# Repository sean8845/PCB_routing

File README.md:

# **PCB\_routing**

## Basic Astar

### Execution Workflow
The routing process is divided into two main stages: clearing the board and generating new routes.

#### 1\. Clear Existing Tracks (Rip-up)

- Before running the routing algorithm, you must remove any existing tracks or vias to create a clean workspace.
- **Script**: basic\_Astar/ripup.py
- **Action**: This script reads your original .kicad\_pcb file, strips away all pre-existing routing data, and saves a clean version to be used as the input for the router.

#### 2\. Execute A\* Routing Logic

- Once the board is clear, you can run the pathfinding algorithm to connect the netlist.
- **Available Scripts**:

    -- **routing\_4direction.py**: Restricts routing to horizontal and vertical movements only. Only 2-Layers is allowed.

    -- **routing_8direction.py**: Allows diagonal movement for more efficient and flexible paths. Only 2-Layers is allowed.

    -- **routing_8direction_multi_layer.py**: Allows multi-layers.
    
- **Action**: The script calculates the shortest path between pins based on grid coordinates and writes the new track data back into a KiCad-compatible file.

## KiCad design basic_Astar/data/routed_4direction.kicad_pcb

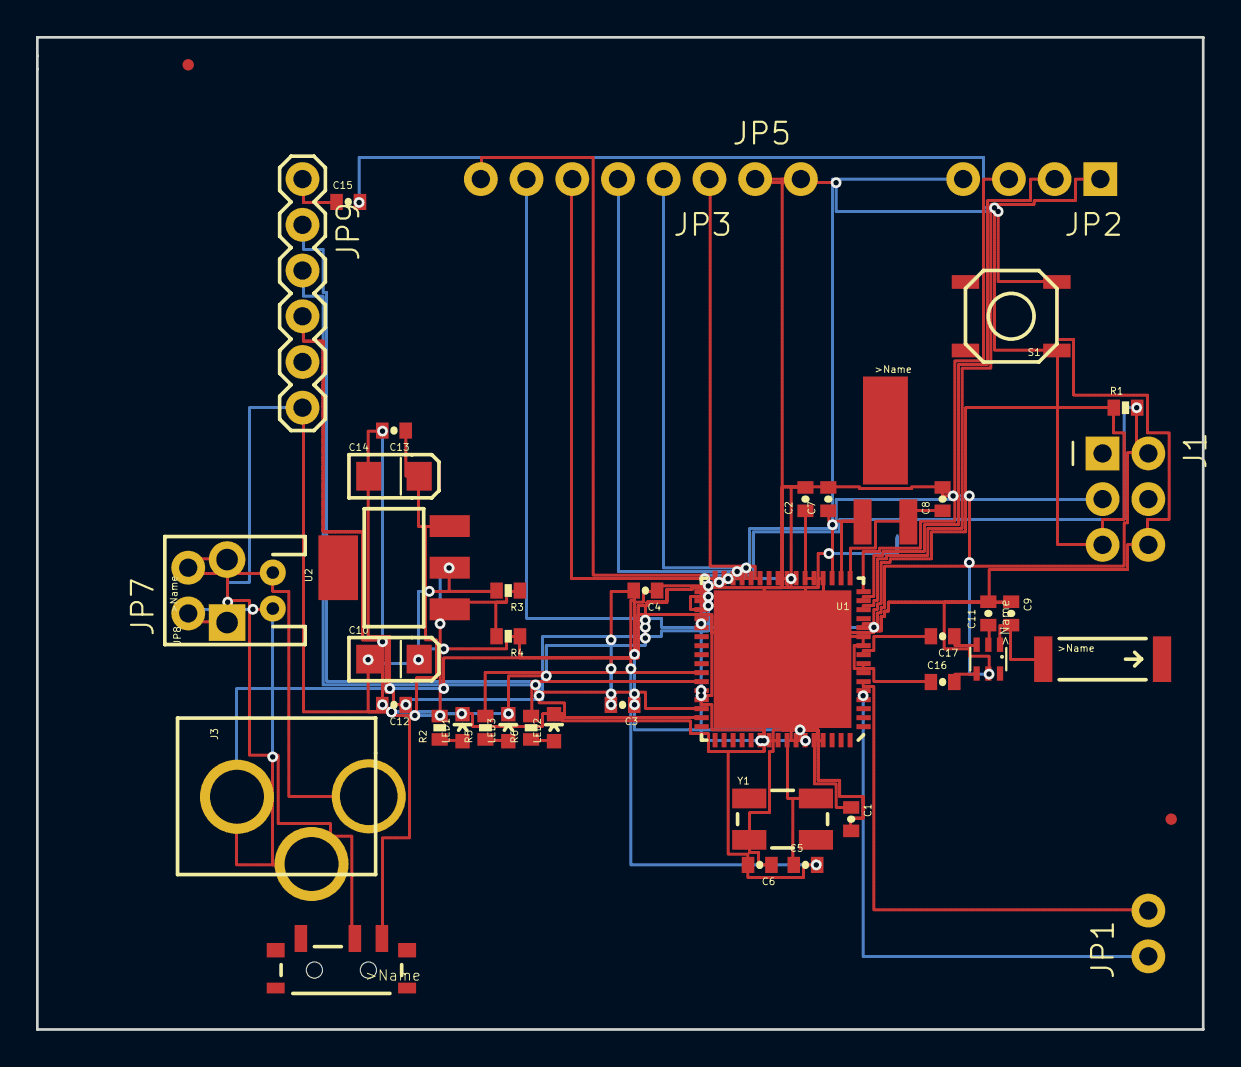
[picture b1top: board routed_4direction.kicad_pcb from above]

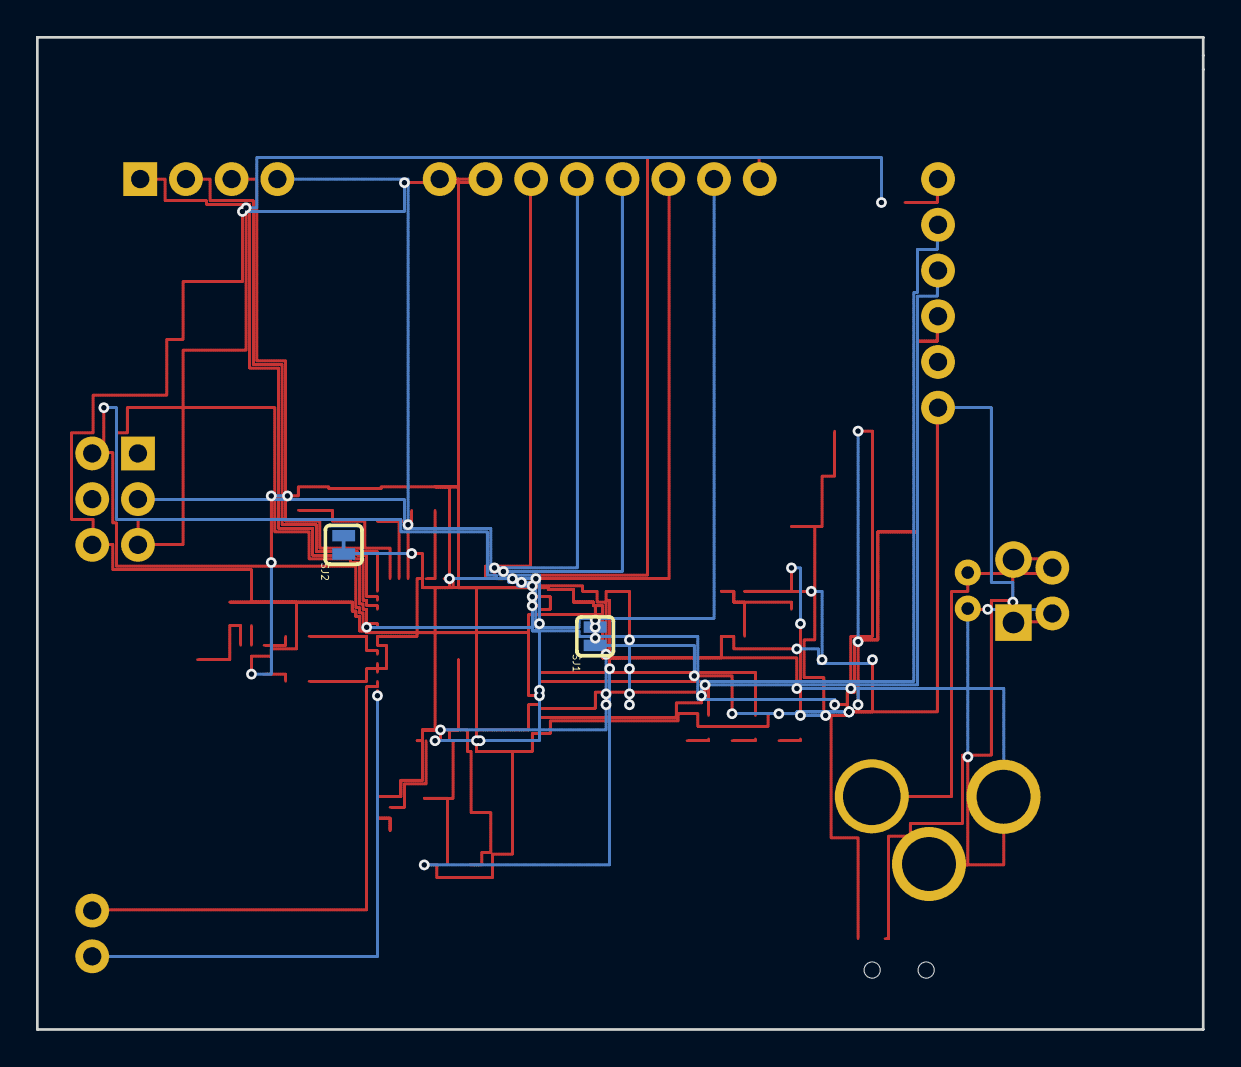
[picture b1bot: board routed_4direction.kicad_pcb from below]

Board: 2 copper layers, 64.8 x 55.1 mm, 48 parts (2 on the bottom side), 39 nets.

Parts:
A1: ANTENNA2SMD5; ANTENNA-CHIP5
B1: 748421245; BALUN
C1, C2, C3, C4, C12: 1uF; 0402-CAP
C5, C6, C7, C8: 12pF; 0402-CAP
C9: 0.75pF; 0402-CAP
C10, C14: 10uF; EIA3216
C11: 22pF; 0402-CAP
C13, C15: 0.1uF; 0402-CAP
C16, C17: JUMP; 0402-CAP
FID1, FID2: FIDUCIALUFIDUCIAL; MICRO-FIDUCIAL
J1: ISP; 2X3-NS
J3: POWER_JACKPTH_LOCK; POWER_JACK_PTH_LOCK
JP1, JP5, JP7: 1X02_NO_SILK
JP2: 1X04_NO_SILK
JP3: 1X06_NS
JP6: JST-2-PTH
JP8: SCREWTERMINAL-3.5MM-2-NS
JP9: FTDI; FTDI_BASIC
LED1: RED; LED-0603
LED2, LED3: GREEN; LED-0603
R1: 10k; 0402-RES
R2: 1k; 0402-RES
R3: 240; 0402-RES
R4: 390; 0402-RES
R5, R6: 330; 0402-RES
S1: TACTILE_SWITCH_SMD
S2: SWITCH-SPST-SMD-A
SJ1, SJ2: SJ_2S-TRACE
U1: ATMEGA128RFA1; QFN-64
U2: LM1117; SOT223
Y1: 16MHz; CRYSTAL-SMD-5X3
Y2: 32.768kHz; CRYSTAL-32KHZ-SMD

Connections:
3.3V: C3.1, C4.1, C10.A, C12.1, J1.2, JP9.VCC, R1.2, R2.2, R3.2, U1.23, U1.34, U1.44, U1.54, U1.59, U2.2
A6: JP1.1, U1.5
A7: JP1.2, U1.6
AVDD: C1.1, U1.60
DTR: C15.1, JP9.DTR
DVDD: C2.1, U1.21, U1.22
FB: R3.1, R4.2, U2.1
GND: B1.5, C1.2, C2.2, C3.2, C4.2, C5.2, C6.2, C7.2, C8.2, C9.1, C10.C, C11.2, C12.2, C13.2, C14.C, J1.6, J3.GND, J3.GNDBREAK, JP5.1, JP5.2, JP6.1, JP7.1, JP8.1, JP9.GND, LED1.C, LED2.C, LED3.C, R4.1, S1.3, SJ1.1, SJ1.2, SJ2.1, SJ2.2, U1.7, U1.10, U1.11, U1.20, U1.24, U1.33, U1.35, U1.45, U1.55, U1.58, U1.61, U1.65
unnamed: LED1.A, R2.1
unnamed: C5.1, U1.57, Y1.3
unnamed: C6.1, U1.56, Y1.1
unnamed: C7.1, U1.18, Y2.X1
unnamed: C8.1, U1.17, Y2.X2
unnamed: B1.2, C11.1
unnamed: LED3.A, R5.1
unnamed: J3.PWR, JP6.2, JP7.2, JP8.2, S2.2
unnamed: B1.4, C16.2
unnamed: B1.3, C17.1
unnamed: LED2.A, R6.1
PB6: R5.2, U1.42
PB7: R6.2, U1.43
PD4: JP3.3, U1.29
PD5: JP3.4, U1.30
PD6: JP3.5, U1.31
PD7: JP3.6, U1.32
PG0: JP2.1, U1.14
PG1: JP2.2, U1.15
PG2: JP2.3, U1.16
PG5: JP2.4, U1.19
RESET: C15.2, J1.5, R1.1, S1.1, U1.12
RFANT: A1.FEED, B1.1, C9.2
RFN: C17.2, U1.9
RFP: C16.1, U1.8
RX0: JP9.TXO, U1.46
RX1: JP3.1, U1.27
SCK: J1.3, U1.37
TX0: JP9.RXI, U1.47
TX1: JP3.2, U1.28
VCC: C13.1, C14.A, S2.1, U2.3

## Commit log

2026-04-15 clear_routing
2026-04-15 basic_astar
2026-04-15 md_v0
2026-04-15 md_v0.1
2026-04-15 md_v0.2
2026-04-15 md_v0.3
2026-04-16 basic_Astar_2Layers
2026-04-16 basic Astar muliti-layer
2026-04-16 md_v0.4
    Updated formatting for script descriptions in README.
